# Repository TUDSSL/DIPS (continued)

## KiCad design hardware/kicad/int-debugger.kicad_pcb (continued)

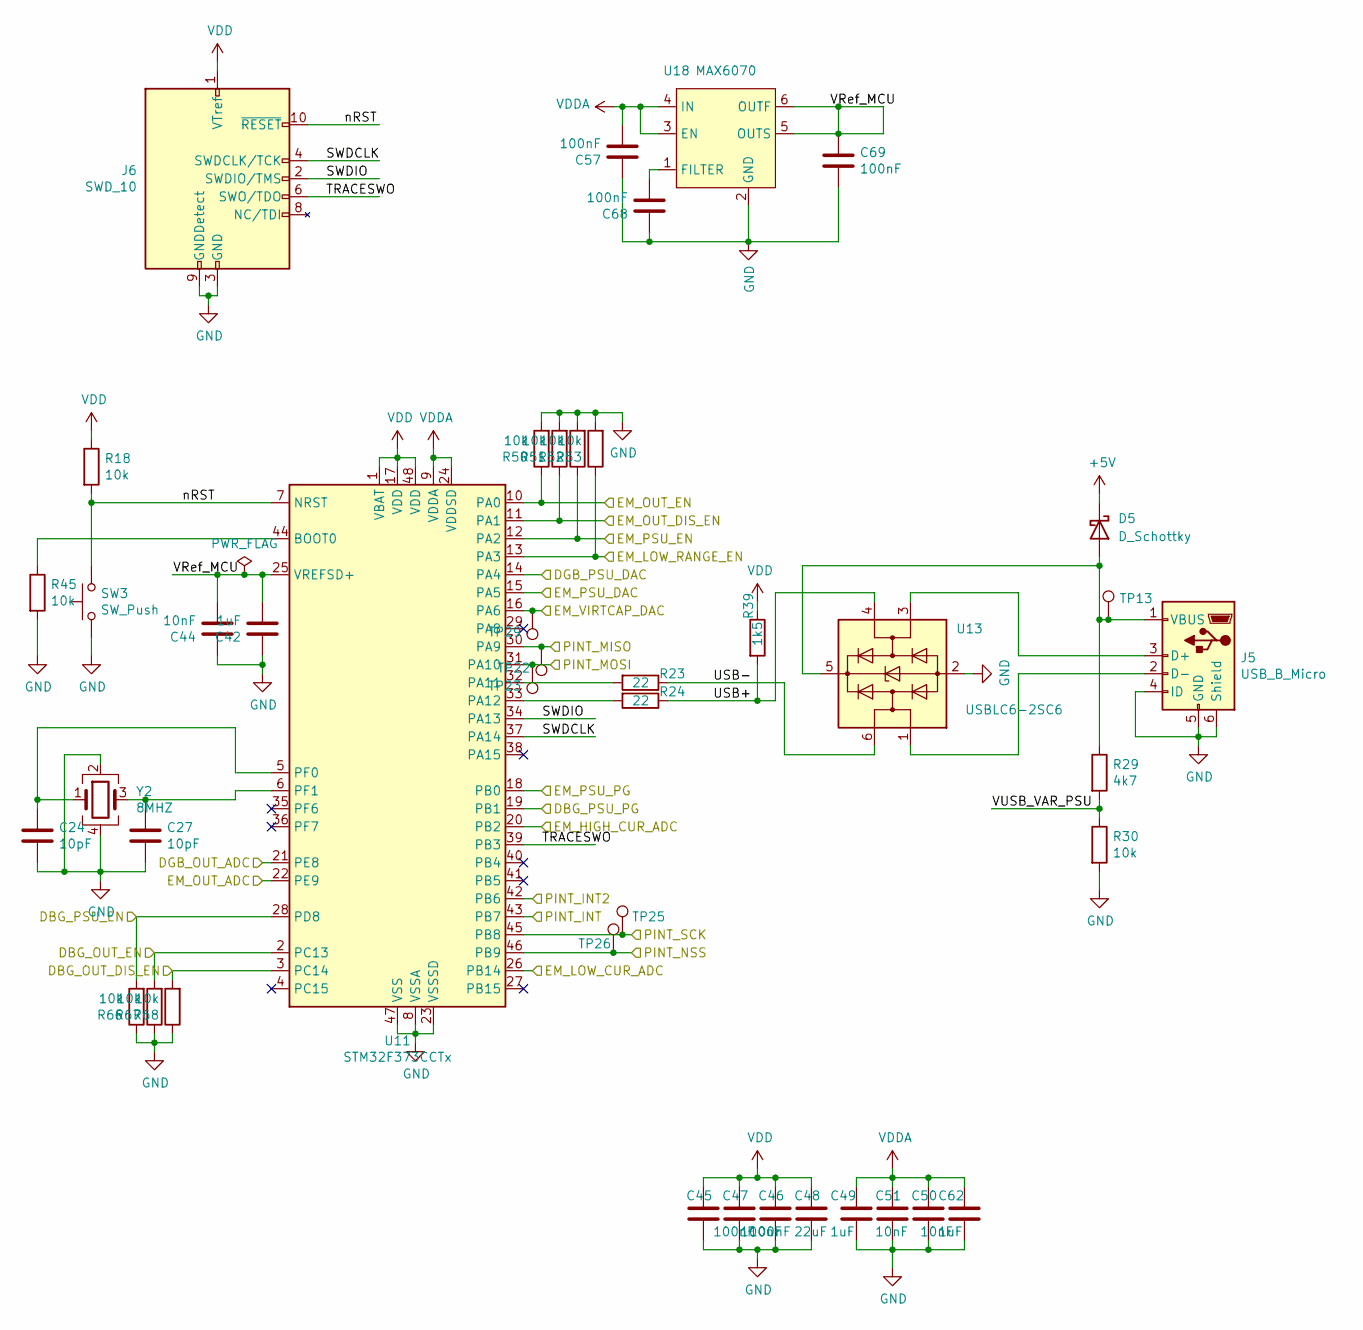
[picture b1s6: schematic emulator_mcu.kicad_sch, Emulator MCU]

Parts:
C24, C27: 10pF; C_0603_1608Metric; MPN CC0603CRNPO9BN100
C42, C49, C62: 1uF; C_0603_1608Metric; MPN TMK107B7105KA-T
C44, C50, C51: 10nF; C_0603_1608Metric; MPN 06035C103KAT2A
C45, C46, C47, C57, C68, C69: 100nF; C_0603_1608Metric; MPN CL10B104KB8NNNC
C48: 22uF; C_0603_1608Metric; MPN GRM188R61A226ME15D
D5: D_Schottky; D_SOD-323F; MPN PMEG6002EJ,115
J5: USB_B_Micro; USB_Micro-B_Molex-105017-0001; MPN 105017-0001
J6: SWD_10; ftsh-105-01-f-dv-k; MPN ftsh-105-01-f-dv-k
R18, R30, R45, R50, R51, R52, R53, R66, R67, R68: 10k; R_0603_1608Metric; MPN RC0603FR-0710KL
R23, R24: 22; R_0603_1608Metric; MPN RC0603FR-0722RL
R29: 4k7; R_0603_1608Metric; MPN RC0603FR-074K7L
R39: 1k5; R_0603_1608Metric; MPN RC0603FR-071K5L
SW3: SW_Push; SW_SPST_B3U-1000P; MPN B3U-1000P
TP13: TestPoint; TestPoint_Keystone_5000-5004_Miniature
TP22, TP23, TP25, TP26, TP29: S2761-46R; MPN S2761-46R
U11: STM32F373CCTx; LQFP-48_7x7mm_P0.5mm; MPN STM32F373CCT
U13: USBLC6-2SC6; SOT-23-6; MPN USBLC6-2SC6
U18: MAX6070; SOT-23-6; MPN MAX6070AAUT30+T
Y2: 8MHZ; Crystal_SMD_Abracon_ABM3B-4Pin_5.0x3.2mm; MPN ABM3B-8.000MHZ-10-D-1-G-T

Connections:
+5V: D5.1 (K); also elsewhere on the board
/Debugger/PINT_INT: U11.43 (PB7); also elsewhere on the board
/Debugger/PINT_MISO: TP22.1, U11.30 (PA9); also elsewhere on the board
/Debugger/PINT_MOSI: TP23.1, U11.31 (PA10); also elsewhere on the board
/Debugger/PINT_NSS: TP26.1, U11.46 (PB9); also elsewhere on the board
/Debugger/PINT_SCK: TP25.1, U11.45 (PB8); also elsewhere on the board
/Emulator/EM_VIRTCAP_DAC: TP29.1, U11.16 (PA6); also elsewhere on the board
/Emulator/Emulator MCU/DBG_OUT_DIS_EN: R68.2, U11.3 (PC14); also elsewhere on the board
/Emulator/Emulator MCU/DBG_OUT_EN: R67.2, U11.2 (PC13); also elsewhere on the board
/Emulator/Emulator MCU/DBG_PSU_EN: R66.2, U11.28 (PD8); also elsewhere on the board
/Emulator/Emulator MCU/DBG_PSU_PG: U11.19 (PB1); also elsewhere on the board
/Emulator/Emulator MCU/DGB_OUT_ADC: U11.21 (PE8); also elsewhere on the board
/Emulator/Emulator MCU/DGB_PSU_DAC: U11.14 (PA4); also elsewhere on the board
/Emulator/Emulator MCU/EM_HIGH_CUR_ADC: U11.20 (PB2); also elsewhere on the board
/Emulator/Emulator MCU/EM_LOW_CUR_ADC: U11.26 (PB14); also elsewhere on the board
/Emulator/Emulator MCU/EM_LOW_RANGE_EN: R53.1, U11.13 (PA3); also elsewhere on the board
/Emulator/Emulator MCU/EM_OUT_ADC: U11.22 (PE9); also elsewhere on the board
/Emulator/Emulator MCU/EM_OUT_DIS_EN: R51.1, U11.11 (PA1); also elsewhere on the board
/Emulator/Emulator MCU/EM_OUT_EN: R50.1, U11.10 (PA0); also elsewhere on the board
/Emulator/Emulator MCU/EM_PSU_DAC: U11.15 (PA5); also elsewhere on the board
/Emulator/Emulator MCU/EM_PSU_EN: R52.1, U11.12 (PA2); also elsewhere on the board
/Emulator/Emulator MCU/EM_PSU_PG: U11.18 (PB0); also elsewhere on the board
/Emulator/Emulator MCU/PINT_INT2: U11.42 (PB6); also elsewhere on the board
/Emulator/Emulator MCU/SWDCLK: J6.4 (SWDCLK/TCK), U11.37 (PA14)
/Emulator/Emulator MCU/SWDIO: J6.2 (SWDIO/TMS), U11.34 (PA13)
/Emulator/Emulator MCU/TRACESWO: J6.6 (SWO/TDO), U11.39 (PB3)
/Emulator/Emulator MCU/USB+: R24.1, R39.2, U13.4 (I/O2)
/Emulator/Emulator MCU/USB-: R23.1, U13.6 (I/O1)
/Emulator/Emulator MCU/VRef_MCU: C42.2, C44.2, C69.1, U11.25 (VREFSD+), U18.5 (OUTS), U18.6 (OUTF)
/Emulator/Emulator MCU/VUSB_VAR_PSU: R29.2, R30.1
/Emulator/Emulator MCU/nRST: J6.10 (~RESET), R18.2, SW3.2, U11.7 (NRST)
GND: C24.2, C27.2, C42.1, C44.1, C45.2, C46.2, C47.2, C48.2, C49.2, C50.2, C51.2, C57.1, C62.2, C68.1, C69.2, J5.4 (ID), J5.5 (GND), J5.6 (Shield), J6.3 (GND), J6.5 (GND), J6.9 (GNDDetect), R30.2, R45.2, R50.2, R51.2, R52.2, R53.2, R66.1, R67.1, R68.1, SW3.1, U11.8 (VSSA), U11.23 (VSSSD), U11.47 (VSS), U13.2 (GND), U18.2 (GND), Y2.2, Y2.4; also elsewhere on the board
unnamed: D5.2 (A), J5.1 (VBUS), R29.1, TP13.1, U13.5 (VBUS)
unnamed: J5.3 (D+), U13.3 (I/O2)
unnamed: J5.2 (D-), U13.1 (I/O1)
unnamed: R45.1, U11.44 (BOOT0)
unnamed: R23.2, U11.32 (PA11)
unnamed: R24.2, U11.33 (PA12)
unnamed: C24.1, U11.5 (PF0), Y2.1
unnamed: C27.1, U11.6 (PF1), Y2.3
unnamed: C68.2, U18.1 (FILTER)
VDD: C45.1, C46.1, C47.1, C48.1, J6.1 (VTref), R18.1, R39.1, U11.1 (VBAT), U11.17 (VDD), U11.48 (VDD); also elsewhere on the board
VDDA: C49.1, C50.1, C51.1, C57.2, C62.1, U11.9 (VDDA), U11.24 (VDDSD), U18.3 (EN), U18.4 (IN); also elsewhere on the board

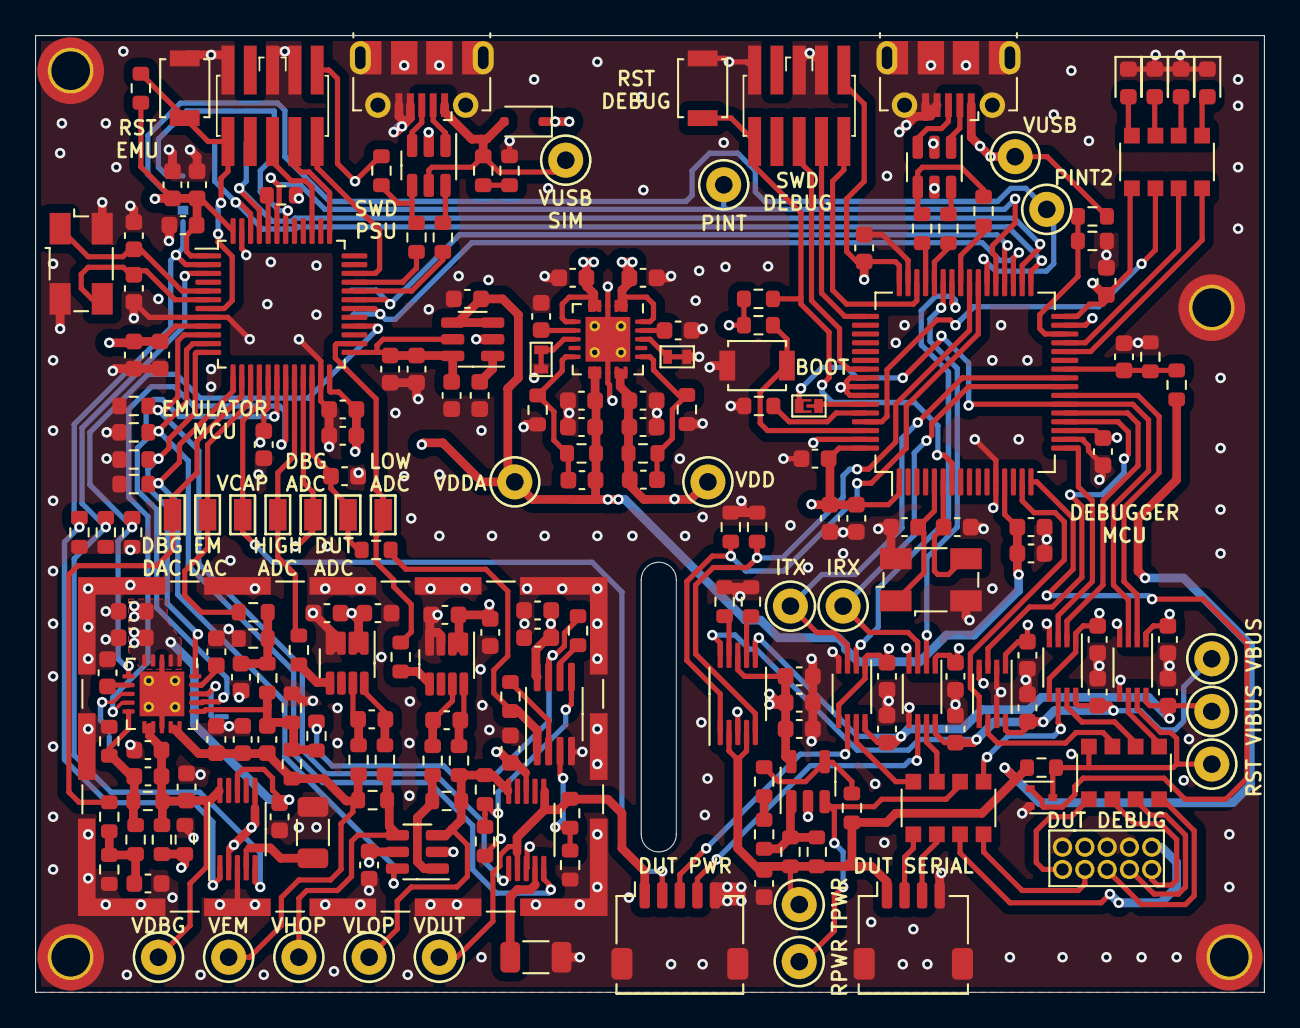
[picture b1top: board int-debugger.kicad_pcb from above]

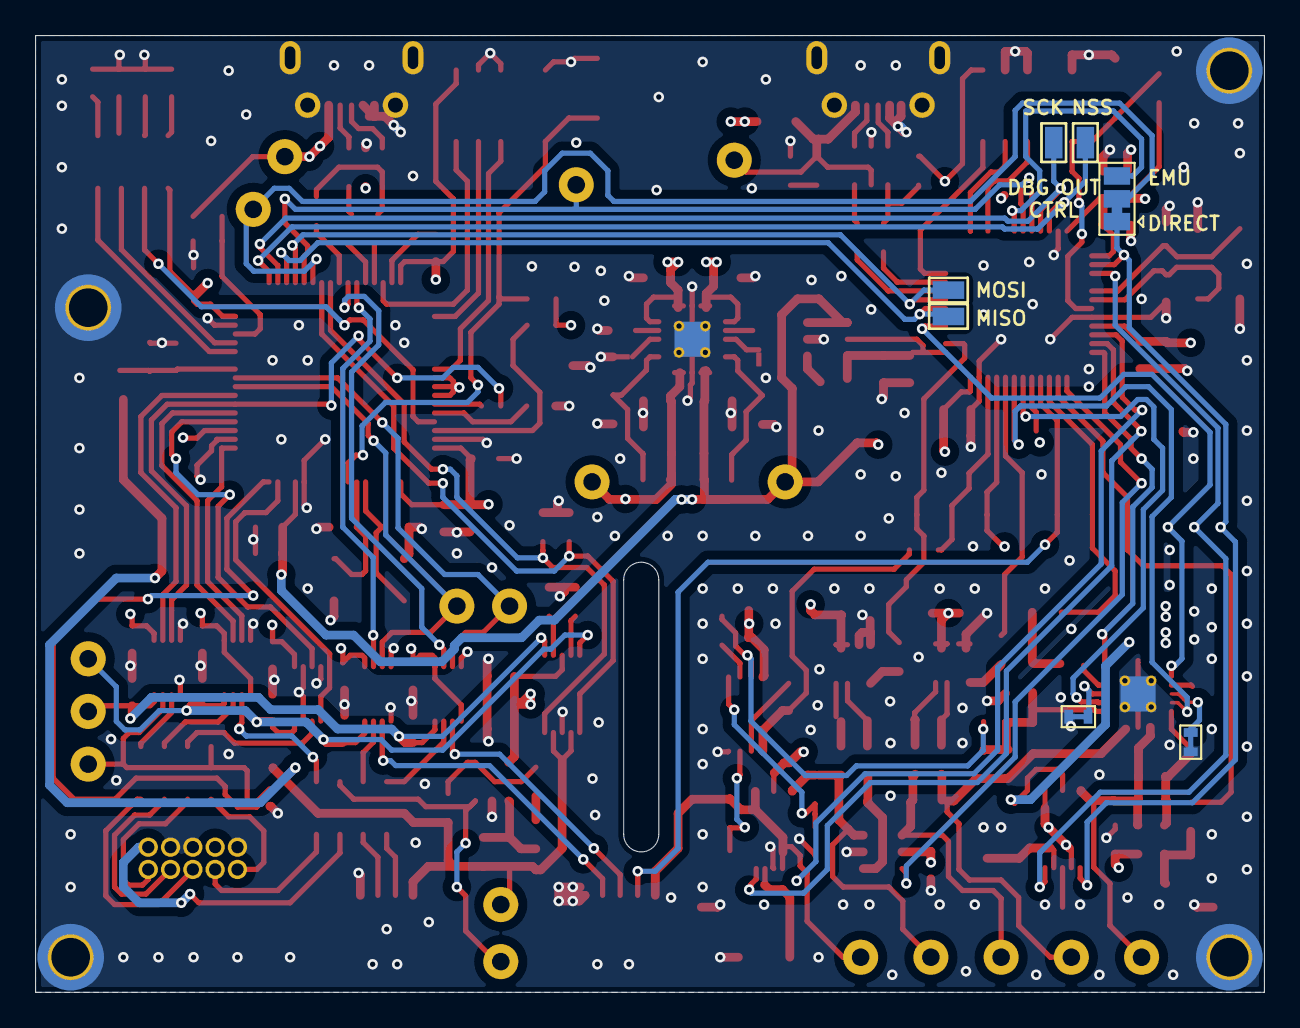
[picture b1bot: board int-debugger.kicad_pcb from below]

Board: 4 copper layers, 70.0 x 54.5 mm, 224 parts (7 on the bottom side), 142 nets.
